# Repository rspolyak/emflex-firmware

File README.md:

# Description
This is the main source code repository of the Emflex firmware.

Emflex was designed to provide users with unified framework for building embedded devices. 
It incorporates RTOS, a set of drivers for different sensors and modules, 
BSP that abstracts application code from underlying boards.

Application code (called "profiles") is meant to incorporate all the capabilities
provided by framework to easily build embedded devices for different areas, like
Home automation, Security, IoT, etc. To ease debugging, Emflex provides CLI and logging components.

## Prerequisites
* Clone or fetch the code repository with all git submodules
  To clone the code repository recursively (git 1.9+)

        git clone --recursive https://github.com/emflex/emflex-firmware.git

    If it is already cloned, manually fetch all the git submodules.

        git submodule update --init --recursive

* Install ARM cross compiler toolchain

## Building
Set building configuration parameters inside make_target file.
You can choose from the following target platforms.

Name                 | Description
-------------------- | ----------------------
ST_STM32L_DISCOVERY  | STM32L Discovery Kit
ST_STM32VL_DISCOVERY | STM32VL Discovery Kit
gtrack               | GSM security board

Also you have to choose one of available profiles.

Name     | Description
-------- | -----------------------
tracking | GSM security device
actuator | Window opening solution

To proceed please execute "make"

## Commiting new changes

Prior to commit new change, ensure existing functionality is not impacted.
Run "./build_targets" to verify compilation of all targets and profiles.

## Burning
* Connect your device to USB port
* Just type "make load" to upload firmware

## Debugging

### Run gdb server
	sudo ./tools/stlink/st-util

### Run ARM gdb
	arm-none-eabi-gdb build/ch.elf
	(gdb) tar extended-remote :4242
	(gdb) load
	(gdb) continue

## [LICENSE](LICENSE)

Unless stated elsewhere, file headers or otherwise, all files herein are licensed under an LGPLv3 license. For more information, please read the LICENSE file.

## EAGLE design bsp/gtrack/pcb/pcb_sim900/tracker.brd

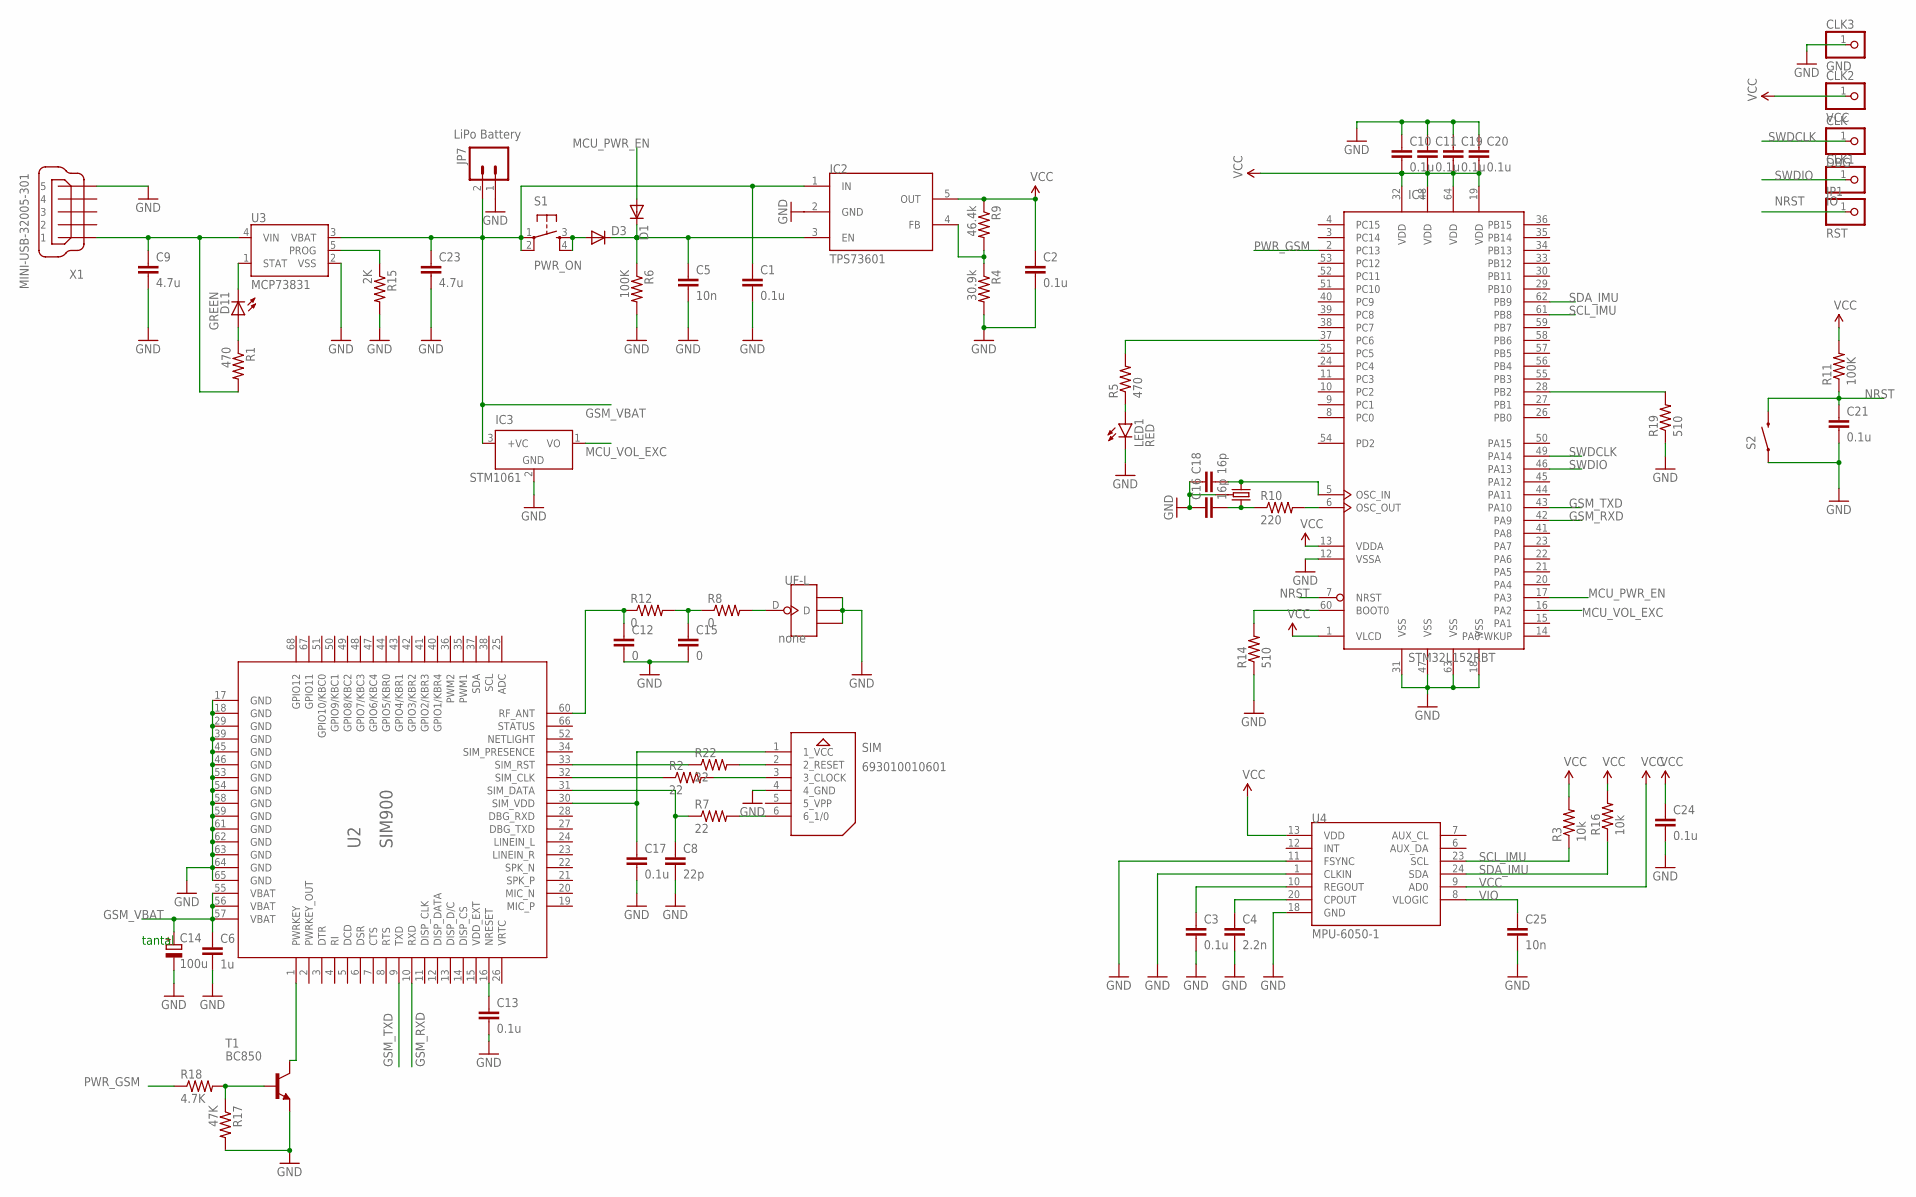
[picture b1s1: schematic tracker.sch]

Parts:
C1, C2, C3, C10, C11, C13, C17, C19, C20, C21, C24: 0.1u; 0805
C4: 2.2n; 0805
C5, C25: 10n; 0805
C6: 1u; 0805
C8: 22p; 0805
C9, C23: 4.7u; 0805
C12, C15: 0; 0805
C14: 100u; C/6032-28R
C16, C18: 16p; 0603-CAP
CLK: DBG; 1X01
CLK1: IO; 1X01
CLK2: VCC; 1X01
CLK3: GND; 1X01
D1, D3: MBR0520LT; SOD123
D11: GREEN; LED-0603
IC1: STM32L152RBT; LQFP64
IC2: TPS73601; SOT23
IC3: LM50; SOT23
JP1: RST; 1X01
JP7: LiPo Battery; JST-2-SMD
LED1: RED; LED-0603
R1, R5: 470; 0805
R2, R7, R22: 22; 0805
R3, R16: 10k; 0805
R4: 30.9k; 0805
R6, R11: 100K; 0805
R8, R12: 0; 0805
R9: 46.4k; 0805
R10: 220; 0805
R14, R19: 510; 0805
R15: 2K; 0805
R17: 47K; 0805
R18: 4.7K; 0805
S1: PWR_ON; TACTILE-PTH
S2: SWITCH-MOMENTARY-2SMD-REDUNDANT; TACTILE-SWITCH-SMD
SIM: 693010010601
T1: BC850; SOT23
U2: SIM900
U3: MCP73831; SOT23-5
U4: MPU-6050-1; QFN-24-4MM2
U$1: CRYSTAL-GROUNDED; CRYSTAL-SMD-5X3
UF-L: none; 4P-U-FL
X1: MINI-USB-32005-301; 32005-301

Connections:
BOOT1: IC1.28 (PB2), R19.2
GND: C1.2, C2.2, C3.2, C4.2, C5.2, C6.2, C8.2, C9.2, C10.1, C11.1, C12.2, C13.2, C14.-, C15.2, C16.1, C17.2, C18.1, C19.1, C20.1, C21.2, C23.2, C24.2, C25.2, CLK3.1, IC1.12 (VSSA), IC1.18 (VSS), IC1.31 (VSS), IC1.47 (VSS), IC1.63 (VSS), IC2.2 (GND), IC3.2 (GND), JP7.1, LED1.C, R4.2, R6.2, R14.1, R15.2, R17.2, R19.1, S2.1, S2.2 (1), SIM.4 (4_GND), T1.2 (E), U2.17 (GND), U2.18 (GND), U2.29 (GND), U2.39 (GND), U2.45 (GND), U2.46 (GND), U2.53 (GND), U2.54 (GND), U2.58 (GND), U2.59 (GND), U2.61 (GND), U2.62 (GND), U2.63 (GND), U2.64 (GND), U2.65 (GND), U3.2 (VSS), U4.1 (CLKIN), U4.11 (FSYNC), U4.18 (GND), U$1.2 (3), U$1.4 (3), UF-L.GND1, UF-L.GND2, UF-L.GND3, X1.5
GSM_RXD: IC1.42 (PA9), U2.10 (RXD)
GSM_TXD: IC1.43 (PA10), U2.9 (TXD)
GSM_VBAT: C1.1, C6.1, C14.+, C23.1, IC2.1 (IN), IC3.3 (+VC), JP7.2, S1.1, S1.2, U2.55 (VBAT), U2.56 (VBAT), U2.57 (VBAT), U3.3 (VBAT)
MCU_PWR_EN: D1.A, IC1.17 (PA3)
MCU_VOL_EXC: IC1.16 (PA2), IC3.1 (VO)
unnamed: C12.1, R12.1, U2.60 (RF_ANT)
unnamed: R7.2, SIM.6 (6_1/0)
unnamed: C13.1, U2.16 (NRESET)
unnamed: C15.1, R8.1, R12.2
unnamed: R2.2, SIM.3 (3_CLOCK)
unnamed: R22.2, SIM.2 (2_RESET)
unnamed: IC1.37 (PC6), R5.2
unnamed: C18.2, IC1.5 (OSC_IN), U$1.3 (1)
unnamed: C16.2, R10.1, U$1.1 (2)
unnamed: R17.1, R18.2, T1.1 (B)
unnamed: D11.A, R1.1
unnamed: IC2.4 (FB), R4.1, R9.2
unnamed: IC1.6 (OSC_OUT), R10.2
unnamed: IC1.60 (BOOT0), R14.2
unnamed: D3.A, S1.3, S1.4
unnamed: T1.3 (C), U2.1 (PWRKEY)
unnamed: LED1.A, R5.1
unnamed: R8.2, UF-L.D
unnamed: C4.1, U4.20 (CPOUT)
unnamed: C3.1, U4.10 (REGOUT)
NRST: C21.1, IC1.7 (NRST), JP1.1, R11.1, S2.3 (2), S2.4 (2)
PROG: R15.1, U3.5 (PROG)
PWR_GSM: IC1.2 (PC13), R18.1
SCL_IMU: IC1.61 (PB8), R3.1, U4.23 (SCL)
SDA_IMU: IC1.62 (PB9), R16.1, U4.24 (SDA)
SIM_CLK: R2.1, U2.32 (SIM_CLK)
SIM_DATA: C8.1, R7.1, U2.31 (SIM_DATA)
SIM_RST: R22.1, U2.33 (SIM_RST)
SIM_VDD: C17.1, SIM.1 (1_VCC), U2.30 (SIM_VDD)
STAT: D11.C, U3.1 (STAT)
SWDCLK: CLK.1, IC1.49 (PA14)
SWDIO: CLK1.1, IC1.46 (PA13)
VCC: C2.1, C10.2, C11.2, C19.2, C20.2, C24.1, CLK2.1, IC1.1 (VLCD), IC1.13 (VDDA), IC1.19 (VDD), IC1.32 (VDD), IC1.48 (VDD), IC1.64 (VDD), IC2.5 (OUT), R3.2, R9.1, R11.2, R16.2, U4.9 (AD0), U4.13 (VDD)
VCC_GSM: C5.1, D1.C, D3.C, IC2.3 (EN), R6.1
VIN1: C9.1, R1.2, U3.4 (VIN), X1.1
VIO: C25.1, U4.8 (VLOGIC)

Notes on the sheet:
tantal
STM1061

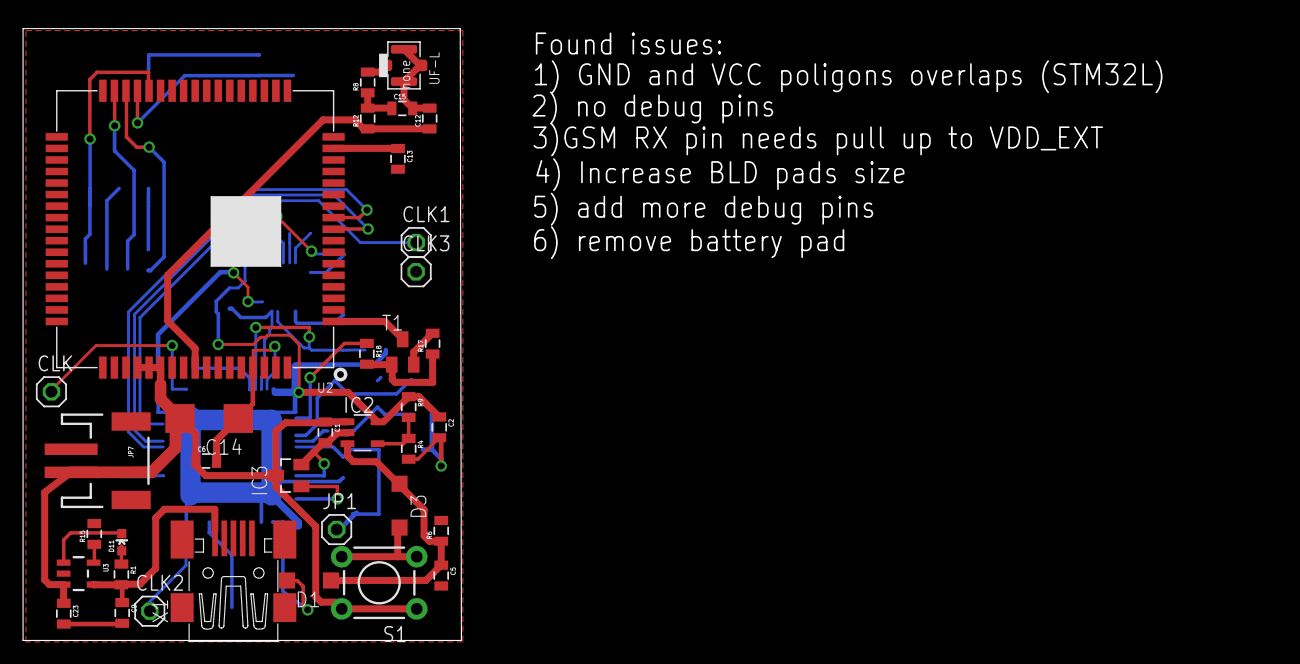
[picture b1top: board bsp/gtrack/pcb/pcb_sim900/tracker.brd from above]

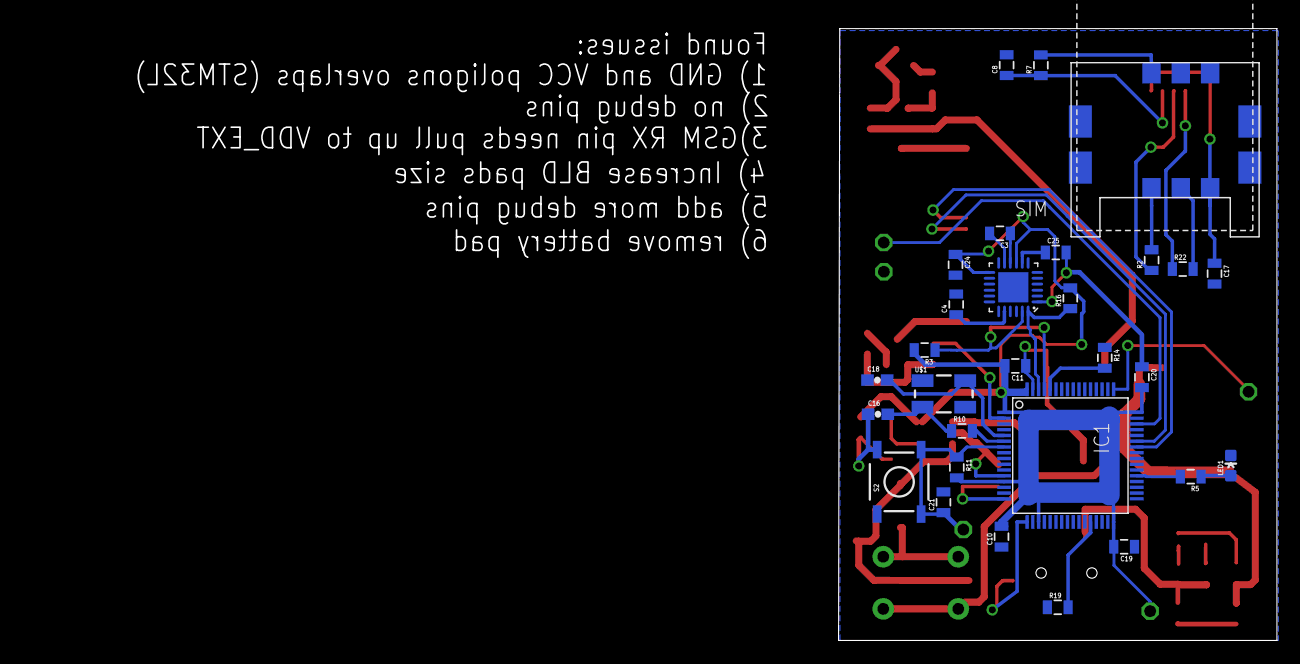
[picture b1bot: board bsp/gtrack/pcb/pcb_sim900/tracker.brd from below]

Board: 2 copper layers, 108.7 x 53.5 mm, 65 parts (29 on the bottom side), 43 nets.

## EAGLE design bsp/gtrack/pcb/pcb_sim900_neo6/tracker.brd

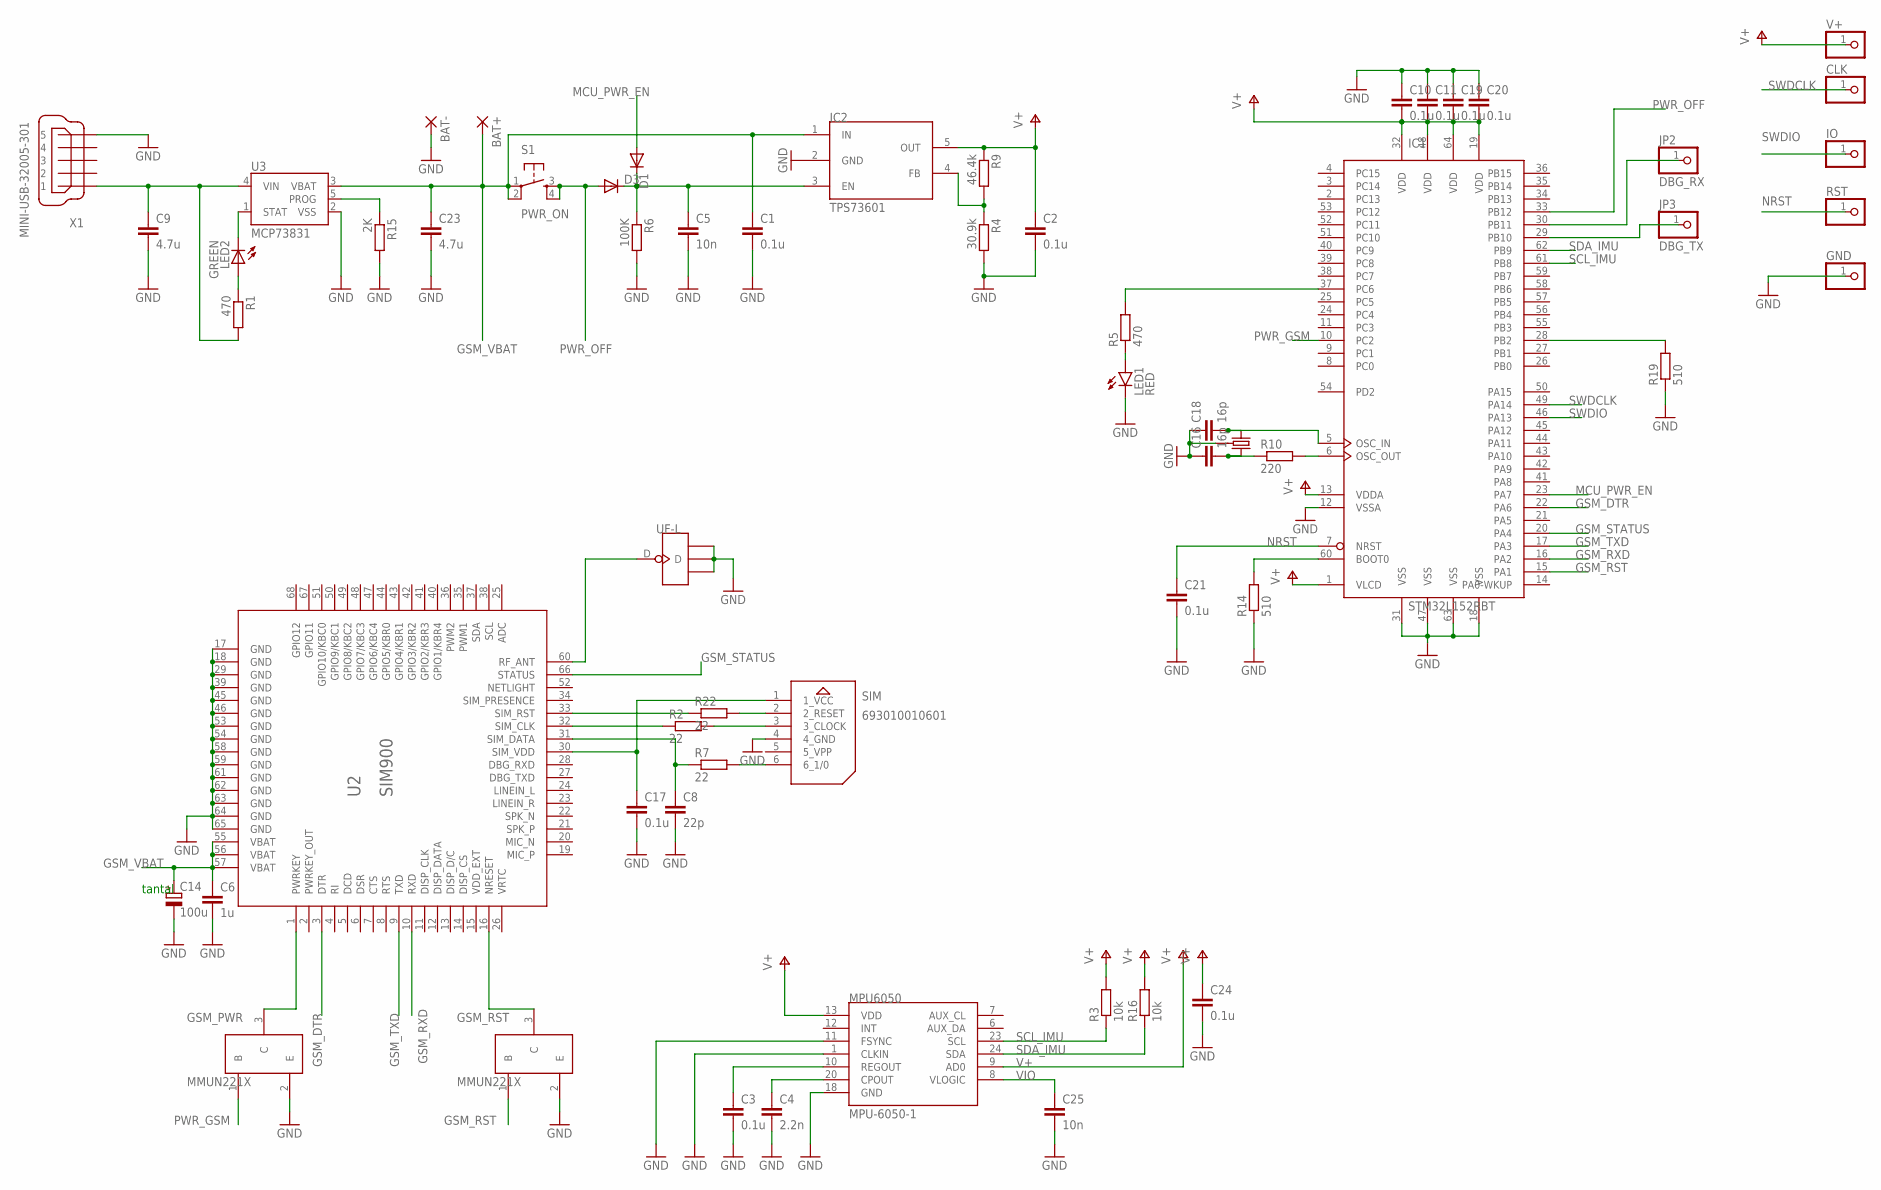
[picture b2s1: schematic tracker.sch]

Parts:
BAT+: SMD2; SMD1,27-2,54
BAT-: SMD2; SMD1,27-2,54
C1, C2, C3, C10, C11, C17, C19, C20, C21, C24: 0.1u; C0805
C4: 2.2n; C0805
C5, C25: 10n; C0805
C6: 1u; C0805
C8: 22p; C0805
C9, C23: 4.7u; C0805
C14: 100u; C/6032-28R
C16, C18: 16p; C0603
CLK: PINHD-1X1; 1X01
CRTL: CRYSTAL-GROUNDED; CRYSTAL-SMD-5X3
D1, D3: MBR0520LT; SOD123
GND: PINHD-1X1; 1X01
GSM_PWR: MMUN221X
GSM_RST: MMUN221X
IC1: STM32L152RBT; LQFP64
IC2: TPS73601; SOT23
IO: PINHD-1X1; 1X01
JP2: DBG_RX; 1X01
JP3: DBG_TX; 1X01
LED1: RED; LED-0603
LED2: GREEN; LED-0603
MPU6050: MPU-6050-1; QFN-24-4MM2
R1, R5: 470; R0805
R2, R7, R22: 22; R0805
R3, R16: 10k; R0805
R4: 30.9k; R0805
R6: 100K; R0805
R9: 46.4k; R0805
R10: 220; R0805
R14, R19: 510; R0805
R15: 2K; R0805
RST: PINHD-1X1; 1X01
S1: PWR_ON; TACTILE-PTH
SIM: 693010010601
U2: SIM900
U3: MCP73831; SOT23-5
UF-L: ANTENNA-U-FL; 4P-U-FL
V+: PINHD-1X1; 1X01
X1: MINI-USB-32005-301; 32005-301

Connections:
BOOT1: IC1.28 (PB2), R19.2
DBG_RX: IC1.30 (PB11), JP2.1
DBG_TX: IC1.29 (PB10), JP3.1
GND: BAT-.1, C1.2, C2.2, C3.2, C4.2, C5.2, C6.2, C8.2, C9.2, C10.1, C11.1, C14.-, C16.1, C17.2, C18.1, C19.1, C20.1, C21.2, C23.2, C24.2, C25.2, CRTL.2 (3), CRTL.4 (3), GND.1, GSM_PWR.2 (E), GSM_RST.2 (E), IC1.12 (VSSA), IC1.18 (VSS), IC1.31 (VSS), IC1.47 (VSS), IC1.63 (VSS), IC2.2 (GND), LED1.C, MPU6050.1 (CLKIN), MPU6050.11 (FSYNC), MPU6050.18 (GND), R4.2, R6.2, R14.1, R15.2, R19.1, SIM.4 (4_GND), U2.17 (GND), U2.18 (GND), U2.29 (GND), U2.39 (GND), U2.45 (GND), U2.46 (GND), U2.53 (GND), U2.54 (GND), U2.58 (GND), U2.59 (GND), U2.61 (GND), U2.62 (GND), U2.63 (GND), U2.64 (GND), U2.65 (GND), U3.2 (VSS), UF-L.GND1, UF-L.GND2, UF-L.GND3, X1.5
GSM_DTR: IC1.22 (PA6), U2.3 (DTR)
GSM_RST: GSM_RST.1 (B), IC1.15 (PA1)
GSM_RXD: IC1.16 (PA2), U2.10 (RXD)
GSM_STATUS: IC1.20 (PA4), U2.66 (STATUS)
GSM_TXD: IC1.17 (PA3), U2.9 (TXD)
GSM_VBAT: BAT+.1, C1.1, C6.1, C14.+, C23.1, IC2.1 (IN), S1.1, S1.2, U2.55 (VBAT), U2.56 (VBAT), U2.57 (VBAT), U3.3 (VBAT)
MCU_PWR_EN: D1.A, IC1.23 (PA7)
unnamed: U2.60 (RF_ANT), UF-L.D
unnamed: R7.2, SIM.6 (6_1/0)
unnamed: GSM_RST.3 (C), U2.16 (NRESET)
unnamed: R2.2, SIM.3 (3_CLOCK)
unnamed: R22.2, SIM.2 (2_RESET)
unnamed: IC1.37 (PC6), R5.2
unnamed: C18.2, CRTL.3 (1), IC1.5 (OSC_IN)
unnamed: C16.2, CRTL.1 (2), R10.1
unnamed: LED2.A, R1.1
unnamed: IC2.4 (FB), R4.1, R9.2
unnamed: IC1.6 (OSC_OUT), R10.2
unnamed: IC1.60 (BOOT0), R14.2
unnamed: GSM_PWR.3 (C), U2.1 (PWRKEY)
unnamed: LED1.A, R5.1
unnamed: C4.1, MPU6050.20 (CPOUT)
unnamed: C3.1, MPU6050.10 (REGOUT)
NRST: C21.1, IC1.7 (NRST), RST.1
PROG: R15.1, U3.5 (PROG)
PWR_GSM: GSM_PWR.1 (B), IC1.10 (PC2)
PWR_OFF: D3.A, IC1.33 (PB12), S1.3, S1.4
SCL_IMU: IC1.61 (PB8), MPU6050.23 (SCL), R3.1
SDA_IMU: IC1.62 (PB9), MPU6050.24 (SDA), R16.1
SIM_CLK: R2.1, U2.32 (SIM_CLK)
SIM_DATA: C8.1, R7.1, U2.31 (SIM_DATA)
SIM_RST: R22.1, U2.33 (SIM_RST)
SIM_VDD: C17.1, SIM.1 (1_VCC), U2.30 (SIM_VDD)
STAT: LED2.C, U3.1 (STAT)
SWDCLK: CLK.1, IC1.49 (PA14)
SWDIO: IC1.46 (PA13), IO.1
V+: C2.1, C10.2, C11.2, C19.2, C20.2, C24.1, IC1.1 (VLCD), IC1.13 (VDDA), IC1.19 (VDD), IC1.32 (VDD), IC1.48 (VDD), IC1.64 (VDD), IC2.5 (OUT), MPU6050.9 (AD0), MPU6050.13 (VDD), R3.2, R9.1, R16.2, V+.1
VCC_GSM: C5.1, D1.C, D3.C, IC2.3 (EN), R6.1
VIN1: C9.1, R1.2, U3.4 (VIN), X1.1
VIO: C25.1, MPU6050.8 (VLOGIC)

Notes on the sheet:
tantal

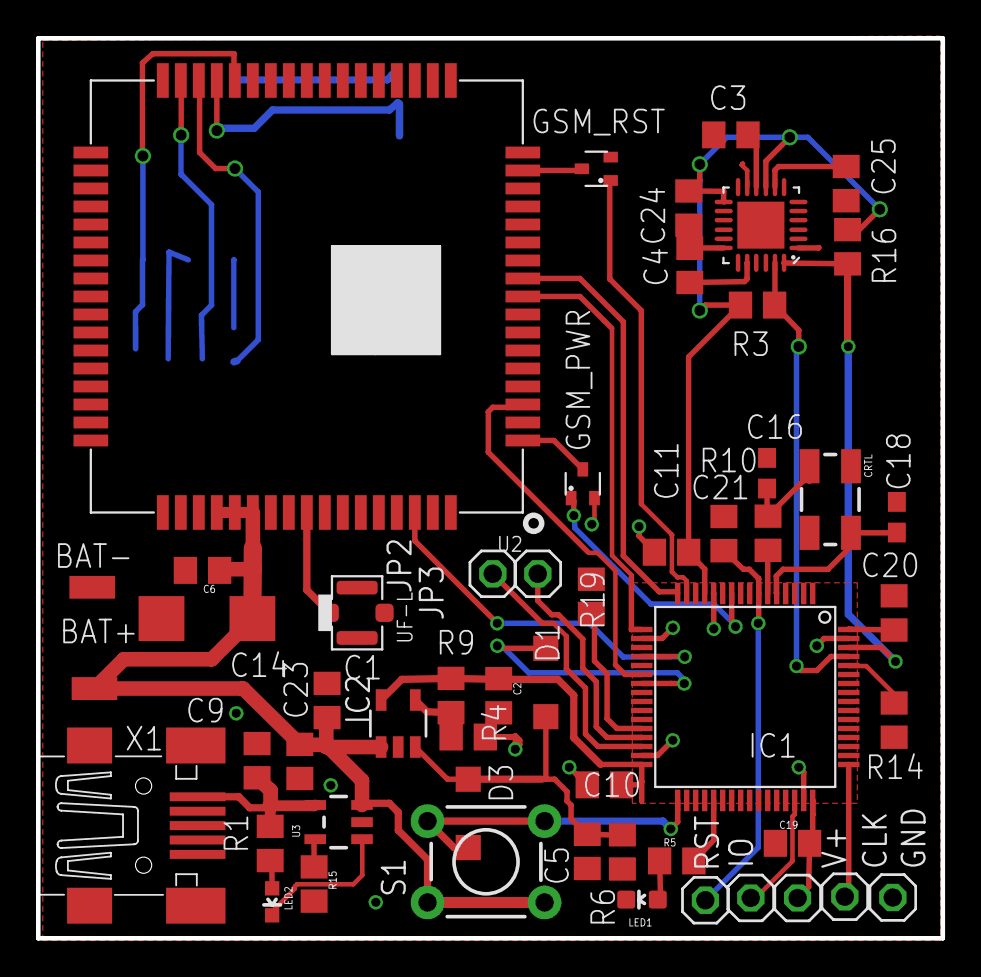
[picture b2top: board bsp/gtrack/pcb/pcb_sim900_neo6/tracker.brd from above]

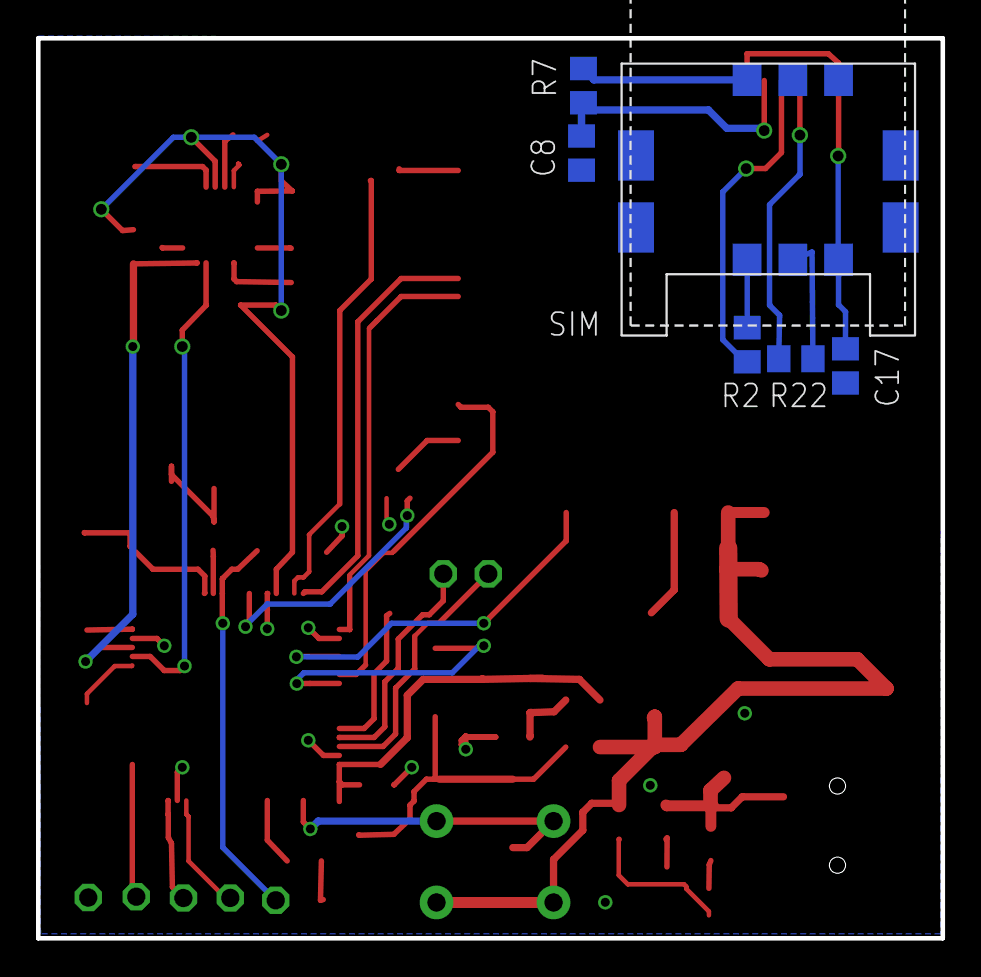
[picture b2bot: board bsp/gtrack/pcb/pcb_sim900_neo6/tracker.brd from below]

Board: 2 copper layers, 50.2 x 50.0 mm, 59 parts (6 on the bottom side), 44 nets.

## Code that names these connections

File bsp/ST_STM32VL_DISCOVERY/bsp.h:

/*****************************************************************************
* File:        bsp.h
*
* Created on:  Dec 27, 2015
*
* Description: platform specific routines for Discovery PCB
*
* Author:      rostokus
******************************************************************************

  This library is free software; you can redistribute it and/or
  modify it under the terms of the GNU Lesser General Public
  License as published by the Free Software Foundation, either
  version 3 of the License, or (at your option) any later version.
  This library is distributed in the hope that it will be useful,
  but WITHOUT ANY WARRANTY; without even the implied warranty of
  MERCHANTABILITY or FITNESS FOR A PARTICULAR PURPOSE.  See the GNU
  Lesser General Public License for more details.
  You should have received a copy of the GNU Lesser General Public
  License along with this library; if not, see <http://www.gnu.org/licenses/>.
******************************************************************************
 */

#ifndef BSP
#define BSP

#include "common.h"

typedef enum
{
  BSP_LOW_VOLTAGE_EVENT = 0,

  BSP_LAST_EVENT
} bsp_event_t;

typedef RV_t (*bsp_cb_t)(void);

extern RV_t bspInit(void);
extern RV_t bspRegisterEventCb(bsp_event_t ev, bsp_cb_t cb);
extern void bspGsmPowerOnOff(void);
extern void bspSystemPowerOff(void);

/**
 * @brief   CLI serial port.
 * @note    Allowed values are SD1, SD2 or SD3.
 * @note    SD1 (PA9 - TX, PA10 - RX)
 */
#define CLI_SERIAL_PORT     SD1

/**
 * @brief   GPS serial port.
 * @note    Allowed values are SD1, SD2 or SD3.
 * @note    SD2 (PA2 - TX, PA3 - RX)
 */
#define GPS_SERIAL_PORT     SD2

/**
 * @brief   WIFI serial port.
 * @note    Allowed values are SD1, SD2 or SD3.
 * @note    SD3 (PB10 - TX, PB11 - RX)
 */
#define WIFI_SERIAL_PORT     SD3

/**
 * @brief   BL serial port.
 * @note    Allowed values are SD1, SD2 or SD3.
 * @note    SD3 (PB10 - TX, PB11 - RX)
 */
#define BL_SERIAL_PORT       SD3

#define GPS_TASK_STACK_SIZE 512

#define CTRL_TASK_STACK_SIZE 512

#define LOGGING_THREAD_STACK_SIZE 512

#define CLI_THREAD_STACK_SIZE 512

#define ACCEL_THREAD_STACK_SIZE 512

#define WIFI_TASK_STACK_SIZE 512


#endif /* BSP */

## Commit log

2016-12-30 Added source code
2016-12-30 Introduced ChibiOS as submodule
2016-12-30 Remove gtrack prototype to be moved to separate repo
2016-12-30 Update README.md file
2017-01-05 Added IMU support
2017-01-06 Update README with Description and Prerequisite sections
2017-01-06 Correct markup bullets
2017-01-08 common : Moved control component outside profile into common folder
2017-01-09 gps : Initial task implementation
2017-01-11 gps : Introduced NMEA parser
2017-01-16 Fixed compilation issue with UART
2017-01-16 Removed redundant drivers from gtrack compilation
2017-01-16 Map gtrack power pin to correct GPIO
2017-01-16 Added license header for gtrack bsp files
2017-01-16 Disable HSE for gtrack BSP (need to revisit later)
2017-01-19 Wifi : Initial commit
2017-01-19 Process device on/off events from power button
2017-01-21 GDB init file
2017-01-21 Set correct GSM power on/off pin; map GSM pins to correct serial driver
2017-01-28 Increase Control task stack size to avoid working area overflow
2017-01-28 Updated GPIO configuration according to board layout
2017-01-28 Fixed GSM driver errors
2017-01-28 Power off GSM module when power off butten is pressed
2017-01-28 Implement status LED support code
2017-01-28 Added BSP initialization complete event to tracking profile
2017-01-30 Readme : Added section on debugging
2017-01-30 accelGyro : Introduced a protection for not inited component
2017-01-31 Let to initialize other devices in case if GSM is not connected
2017-02-01 GSM : Moved configure commands into GSM parser task
2017-02-05 Handle accelerometer events
2017-02-05 Fixed incorrect return code processing
2017-02-05 Updated MPU6050 address
2017-02-05 Reduced accelerometer thread stack size
2017-02-05 Enabled floating points for chprintf
2017-02-06 Fixed issue with STATE command
2017-02-06 Enable GPRS
2017-02-06 Initial commit with STM32F3_DISCOVERY board support
2017-02-06 Enabled missing modules in halconf
2017-02-07 Fixed TIMER PRESCALER compilation issue
2017-02-07 Fixed compilation errors for stepper and eeprom
2017-02-07 STM32F3 : Fixed I2C compilation errors
2017-02-07 Incorporated review comments
2017-02-07 Fix issue with device power off during device power on
2017-02-07 Remove dead code
2017-02-07 Fixed compilation issue for gtrack board
2017-02-08 Fix compilation issue in tracking profile code
2017-02-13 Increase thread stack size
2017-02-13 Enable GSM power safe mode
2017-02-22 Increase IMU threshold level from 0.5 to 1
2017-02-22 Move serialInit() after BSP initialization code
2017-02-22 Decrease low battery threshold level to 3
2017-02-22 Allow to disable Logging component
2017-02-22 Introduced new thread to handle power on/off button events
2017-02-22 Revert "Allow to disable Logging component"
    This reverts commit 4ec51cf59aad0b1e81981b4512931df861761c24.
2017-02-22 Remove not used ChibiOS drivers/options
2017-02-22 Reduce GSM module stack size by 280b
2017-02-26 GPRS : Send battery and signal over https
2017-02-26 GPRS : Fixed battery and signal
2017-02-27 GPRS : Fixed connection issue
2017-03-18 Add option to arm/disarm device via voice call
2017-03-18 Increase IMU threshold
2017-03-21 Update hardcoded accelerometer threshold value with constant
2017-04-02 Code cleanup;memory optimization;GSM driver bug fix
2017-04-05 ST_STM32F3_DISCOVERY : Fixed compilation
2017-04-20 Profiles : Introduced an empty BLE prototype
2017-04-21 STM32VL : Fixed compilation issues
2017-04-21 BLE : Added bidirectional communication
2017-04-21 BL : Removed step motor related code to the actuator profile
2017-04-26 BLE prototype : Initial support for gerkon sensor
2017-04-26 BLE prototype : Introduced a thread inside interrupts controller
2017-04-26 Reduce RAM usage by GSM driver; add buffer overflow checks for GSM cmd parser
2017-04-27 EXT driver : Removed redundant channel activation
2017-04-27 EXT driver : Make thread awake on message received only
2017-04-27 BLE prototype : Added a counter
2017-04-27 EXT driver : Disable a channel until interrupt is processed
2017-05-01 Fixed log message for GSM parser
2017-05-02 Fix error with IMU initialization
2017-05-02 Reduce number of low battery SMSs
2017-05-02 Initial set of files for STM32F103 mini dev board
2017-05-02 Remove redundant code
2017-05-10 Fixed ble_prototype compilation for stm32f103_mini
2017-05-10 Rework power off feature
2017-05-10 Add MT protection for console device
2017-05-11 Fix serial port configuration for STM32F1034 board
2017-05-15 Add script to verify compilation all target and profiles
2017-05-15 Update README.md with correct name for build_targets script
2017-05-15 Implement GSM reset functionality
2017-05-17 Increase power off timing to 5sec
2017-05-17 Increase GSM reset timing to 90sec
2017-05-17 Introduce GSM reset function
2017-05-17 Add possibility to send GSM commands with high priority
2017-05-17 Add more debug messages
2017-05-18 Add more debug/error logs to GSM driver
2017-05-19 Substitute couple of LOG_TRACE macros with LOG_ERROR
2017-05-19 Fix compilation warning
2017-05-19 Use EXT driver instead of direct API calls
2017-05-19 Decrease stack size
2017-05-19 Add compatibility matrix

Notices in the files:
parts and their libraries:
Speicherkarten-SockelWR-CRD: Copyright: Würth Elektronik
SparkFun-Electromechanical: Licensing: Creative Commons ShareAlike 4.0 International - https://creativecommons.org/licenses/by-sa/4.0
